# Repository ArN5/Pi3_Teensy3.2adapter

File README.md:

# Pi3_Teensy3.2adapter
This board connects a raspberry pi 3 to a teensy v3 board, you also get access to all the i/o from the PI3. has a connecter that leads to a Jetson TK1 adapter.
All the devices are connected via the I2C pins. Also there is room for an MPU6050.
This board was made for our original sub for the Robosub competition. 
It would be connected to a jetson tk1 via I2C.

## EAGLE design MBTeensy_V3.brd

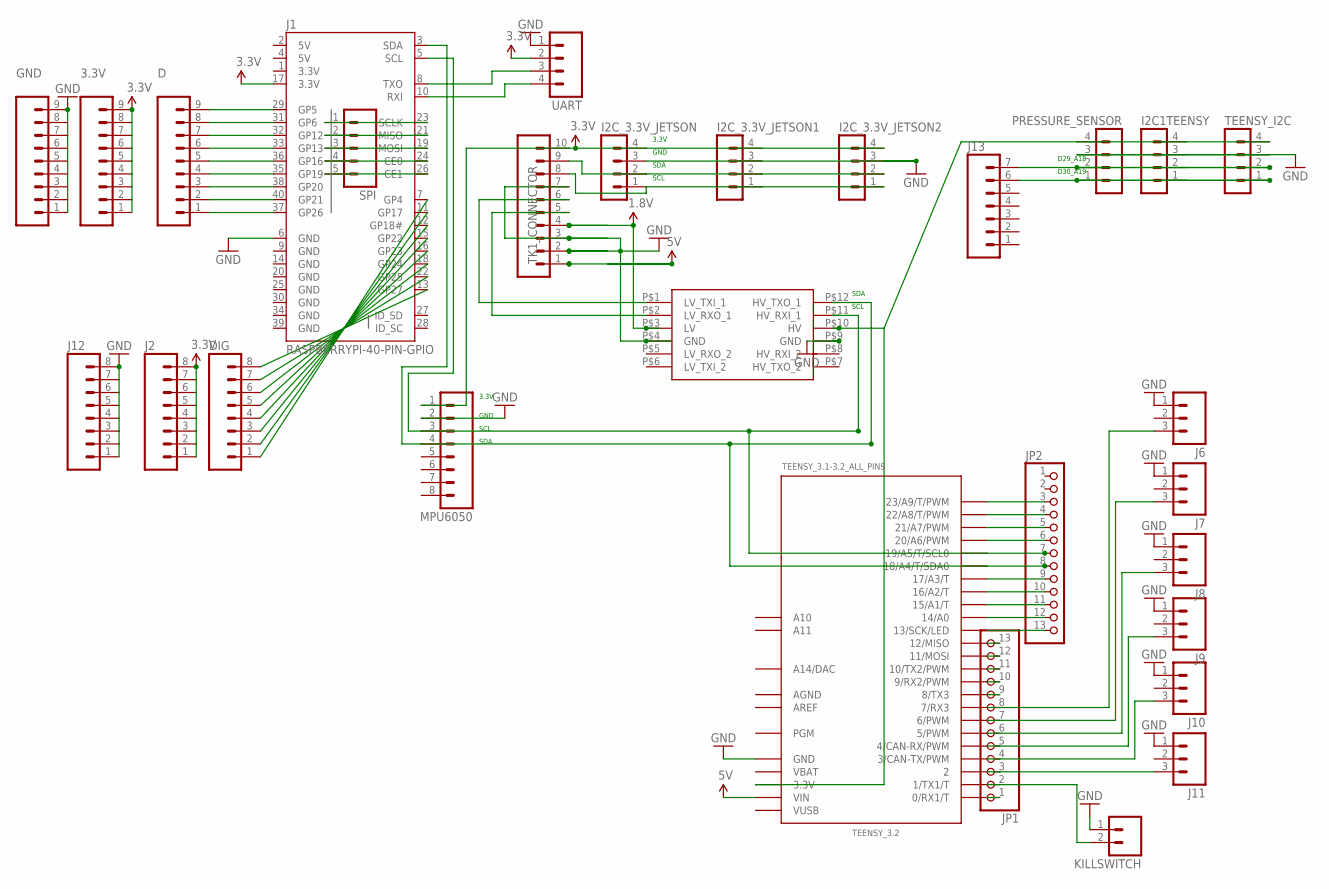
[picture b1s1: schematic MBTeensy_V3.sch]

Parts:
3.3V: M09; 1X09
D: M09; 1X09
DIG: M08; 1X08_ROUND
GND: M09; 1X09
I2C1TEENSY, I2C_3.3V_JETSON, I2C_3.3V_JETSON1, I2C_3.3V_JETSON2: MA04-1
J1: RASPBERRYPI-40-PIN-GPIO; 2X20-SHROUDED
J2, J12: M08; 1X08_ROUND
J6, J7, J8, J9, J10, J11: M03LOCK_LONGPADS; 1X03_LOCK_LONGPADS
J13: M07; 1X07
JP1, JP2: PINHD-1X13; 1X13
KILLSWITCH: M02LOCK_LONGPADS; 1X02_LOCK_LONGPADS
MPU6050: M08LOCK_LONGPADS; 1X08_LOCK_LONGPADS
PRESSURE_SENSOR: MA04-1
SPI: M05PTH; 1X05
TEENSY_3.2: TEENSY_3.1-3.2_ALL_PINS; TEENSY_3.0-3.2&LC_ALL_PINS
TEENSY_I2C: MA04-1
TK1_CONNECTOR: M10LOCK_LONGPADS; 1X10_LOCK_LONGPADS
U$2: LOGIC_LEVEL_CONVERTER
UART: M04PTH; 1X04

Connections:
1.8SCL: TK1_CONNECTOR.5, U$2.P$2 (LV_RXO_1)
1.8SDA: TK1_CONNECTOR.6, U$2.P$1 (LV_TXI_1)
1.8V: TK1_CONNECTOR.4, U$2.P$3 (LV)
3.3V: 3.3V.1, 3.3V.2, 3.3V.3, 3.3V.4, 3.3V.5, 3.3V.6, 3.3V.7, 3.3V.8, 3.3V.9, I2C_3.3V_JETSON.4, I2C_3.3V_JETSON1.4, I2C_3.3V_JETSON2.4, J1.1 (3.3V), J1.17 (3.3V), J2.1, J2.2, J2.3, J2.4, J2.5, J2.6, J2.7, J2.8, MPU6050.1, TK1_CONNECTOR.10, UART.2
3.3V_TEENSY_100MA_MAX: I2C1TEENSY.4, PRESSURE_SENSOR.4, TEENSY_3.2.3.3V, TEENSY_3.2.3.3V1 (3.3V), TEENSY_I2C.4, U$2.P$10 (HV)
3.3_SCL: I2C_3.3V_JETSON.1, I2C_3.3V_JETSON1.1, I2C_3.3V_JETSON2.1, TK1_CONNECTOR.8
3.3_SDA: I2C_3.3V_JETSON.2, I2C_3.3V_JETSON1.2, I2C_3.3V_JETSON2.2, TK1_CONNECTOR.9
5V: J1.2 (5V), J1.4 (5V), TEENSY_3.2.VIN, TK1_CONNECTOR.1
AGND: TEENSY_3.2.AGND
AREF: TEENSY_3.2.AREF
CE0: J1.24 (CE0), SPI.4
CE1: J1.26 (CE1), SPI.5
D0: JP1.1, TEENSY_3.2.0 (0/RX1/T)
D1: JP1.2, KILLSWITCH.2, TEENSY_3.2.1 (1/TX1/T)
D2: J11.3, JP1.3, TEENSY_3.2.2
D3: J10.3, JP1.4, TEENSY_3.2.3 (3/CAN-TX/PWM)
D4: J9.3, JP1.5, TEENSY_3.2.4 (4/CAN-RX/PWM)
D5: J8.3, JP1.6, TEENSY_3.2.5 (5/PWM)
D6: J7.3, JP1.7, TEENSY_3.2.6 (6/PWM)
D7: J6.3, JP1.8, TEENSY_3.2.7 (7/RX3)
D8: JP1.9, TEENSY_3.2.8 (8/TX3)
D9: JP1.10, TEENSY_3.2.9 (9/RX2/PWM)
D10: JP1.11, TEENSY_3.2.10 (10/TX2/PWM)
D11: JP1.12, TEENSY_3.2.11 (11/MOSI)
D12: JP1.13, TEENSY_3.2.12 (12/MISO)
D16: JP2.10, TEENSY_3.2.16/A2 (16/A2/T)
D17: JP2.9, TEENSY_3.2.17/A3 (17/A3/T)
D20: JP2.6, TEENSY_3.2.20/A6 (20/A6/PWM)
D21: JP2.5, TEENSY_3.2.21/A7 (21/A7/PWM)
D22: JP2.4, TEENSY_3.2.22/A8 (22/A8/T/PWM)
D23: JP2.3, TEENSY_3.2.23/A9 (23/A9/T/PWM)
GND: GND.1, GND.2, GND.3, GND.4, GND.5, GND.6, GND.7, GND.8, GND.9, I2C1TEENSY.3, I2C_3.3V_JETSON.3, I2C_3.3V_JETSON1.3, I2C_3.3V_JETSON2.3, J1.6 (GND), J1.9 (GND), J1.14 (GND), J1.20 (GND), J1.25 (GND), J1.30 (GND), J1.34 (GND), J1.39 (GND), J6.1, J7.1, J8.1, J9.1, J10.1, J11.1, J12.1, J12.2, J12.3, J12.4, J12.5, J12.6, J12.7, J12.8, KILLSWITCH.1, MPU6050.2, PRESSURE_SENSOR.3, TEENSY_3.2.GND, TEENSY_3.2.GND1 (GND), TEENSY_I2C.3, TK1_CONNECTOR.2, TK1_CONNECTOR.3, TK1_CONNECTOR.7, U$2.P$4 (GND), U$2.P$9 (GND), UART.1
GP4: DIG.1, J1.7 (GP4)
GP5: D.9, J1.29 (GP5)
GP6: D.8, J1.31 (GP6)
GP12: D.7, J1.32 (GP12)
GP13: D.6, J1.33 (GP13)
GP16: D.5, J1.36 (GP16)
GP17: DIG.2, J1.11 (GP17)
GP18: DIG.3, J1.12 (GP18#)
GP19: D.4, J1.35 (GP19)
GP20: D.3, J1.38 (GP20)
GP21: D.2, J1.40 (GP21)
GP22: DIG.4, J1.15 (GP22)
GP23: DIG.5, J1.16 (GP23)
GP24: DIG.6, J1.18 (GP24)
GP25: DIG.7, J1.22 (GP25)
GP26: D.1, J1.37 (GP26)
GP27: DIG.8, J1.13 (GP27)
MISO: J1.21 (MISO), SPI.2
MOSI: J1.19 (MOSI), SPI.3
unnamed: JP2.13, TEENSY_3.2.13 (13/SCK/LED)
unnamed: JP2.12, TEENSY_3.2.14/A0
unnamed: JP2.11, TEENSY_3.2.15/A1 (15/A1/T)
RX_PI: J1.10 (RXI), UART.4
SCL0_TEENSY: J1.5 (SCL), JP2.7, MPU6050.3, TEENSY_3.2.19/A5 (19/A5/T/SCL0), U$2.P$11 (HV_RXI_1)
SCL1: I2C1TEENSY.2, J13.7, PRESSURE_SENSOR.2, TEENSY_I2C.2
SCLK: J1.23 (SCLK), SPI.1
SDA0_TEENSY: J1.3 (SDA), JP2.8, MPU6050.4, TEENSY_3.2.18/A4 (18/A4/T/SDA0), U$2.P$12 (HV_TXO_1)
SDA1: I2C1TEENSY.1, J13.6, PRESSURE_SENSOR.1, TEENSY_I2C.1
TX_PI: J1.8 (TXO), UART.3
VBAT: TEENSY_3.2.VBAT
VUSB: TEENSY_3.2.VUSB

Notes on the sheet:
SDA
SCL
3.3V
GND
D30_A19
D29_A18

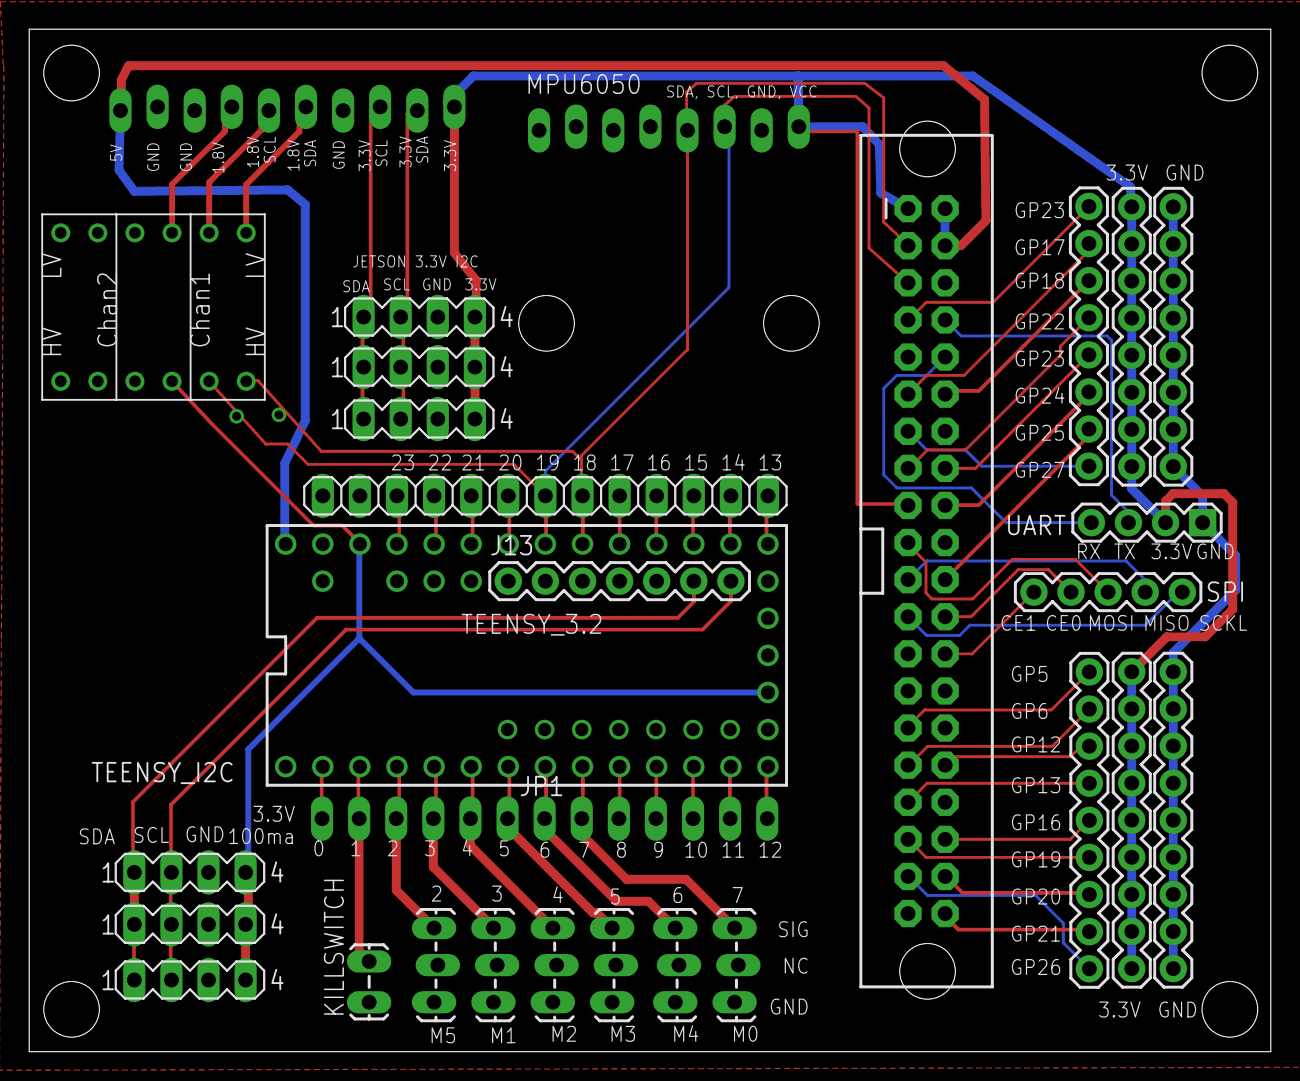
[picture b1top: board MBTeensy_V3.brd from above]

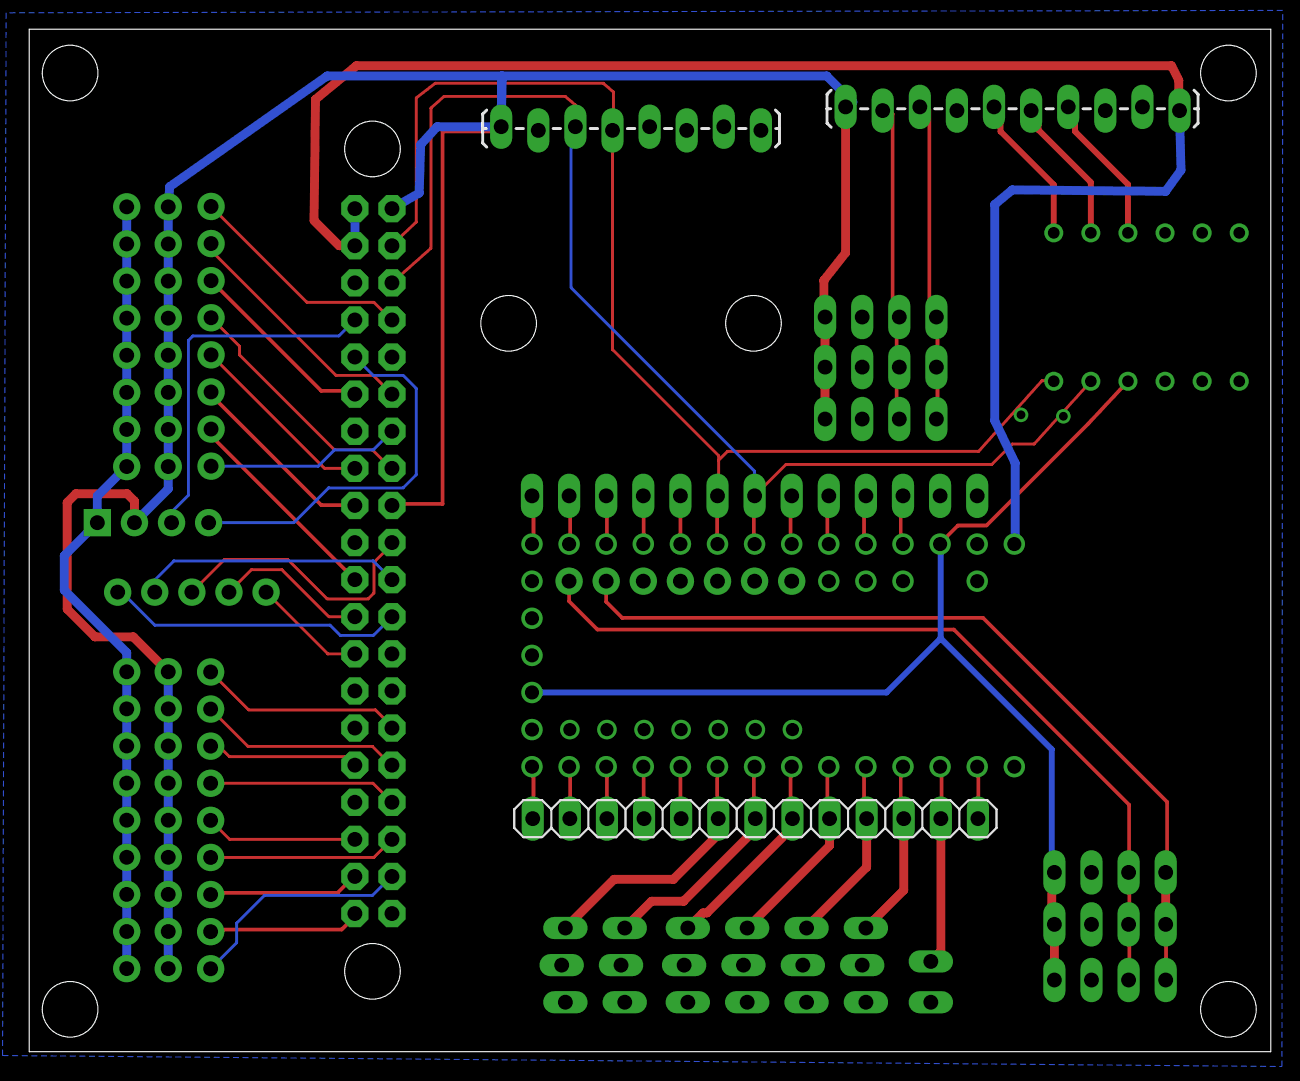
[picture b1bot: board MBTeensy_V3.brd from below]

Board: 2 copper layers, 85.0 x 70.0 mm, 29 parts (3 on the bottom side), 59 nets.

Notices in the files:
parts and their libraries:
SparkFun-Boards: Licensing: Creative Commons ShareAlike 4.0 International - https://creativecommons.org/licenses/by-sa/4.0
